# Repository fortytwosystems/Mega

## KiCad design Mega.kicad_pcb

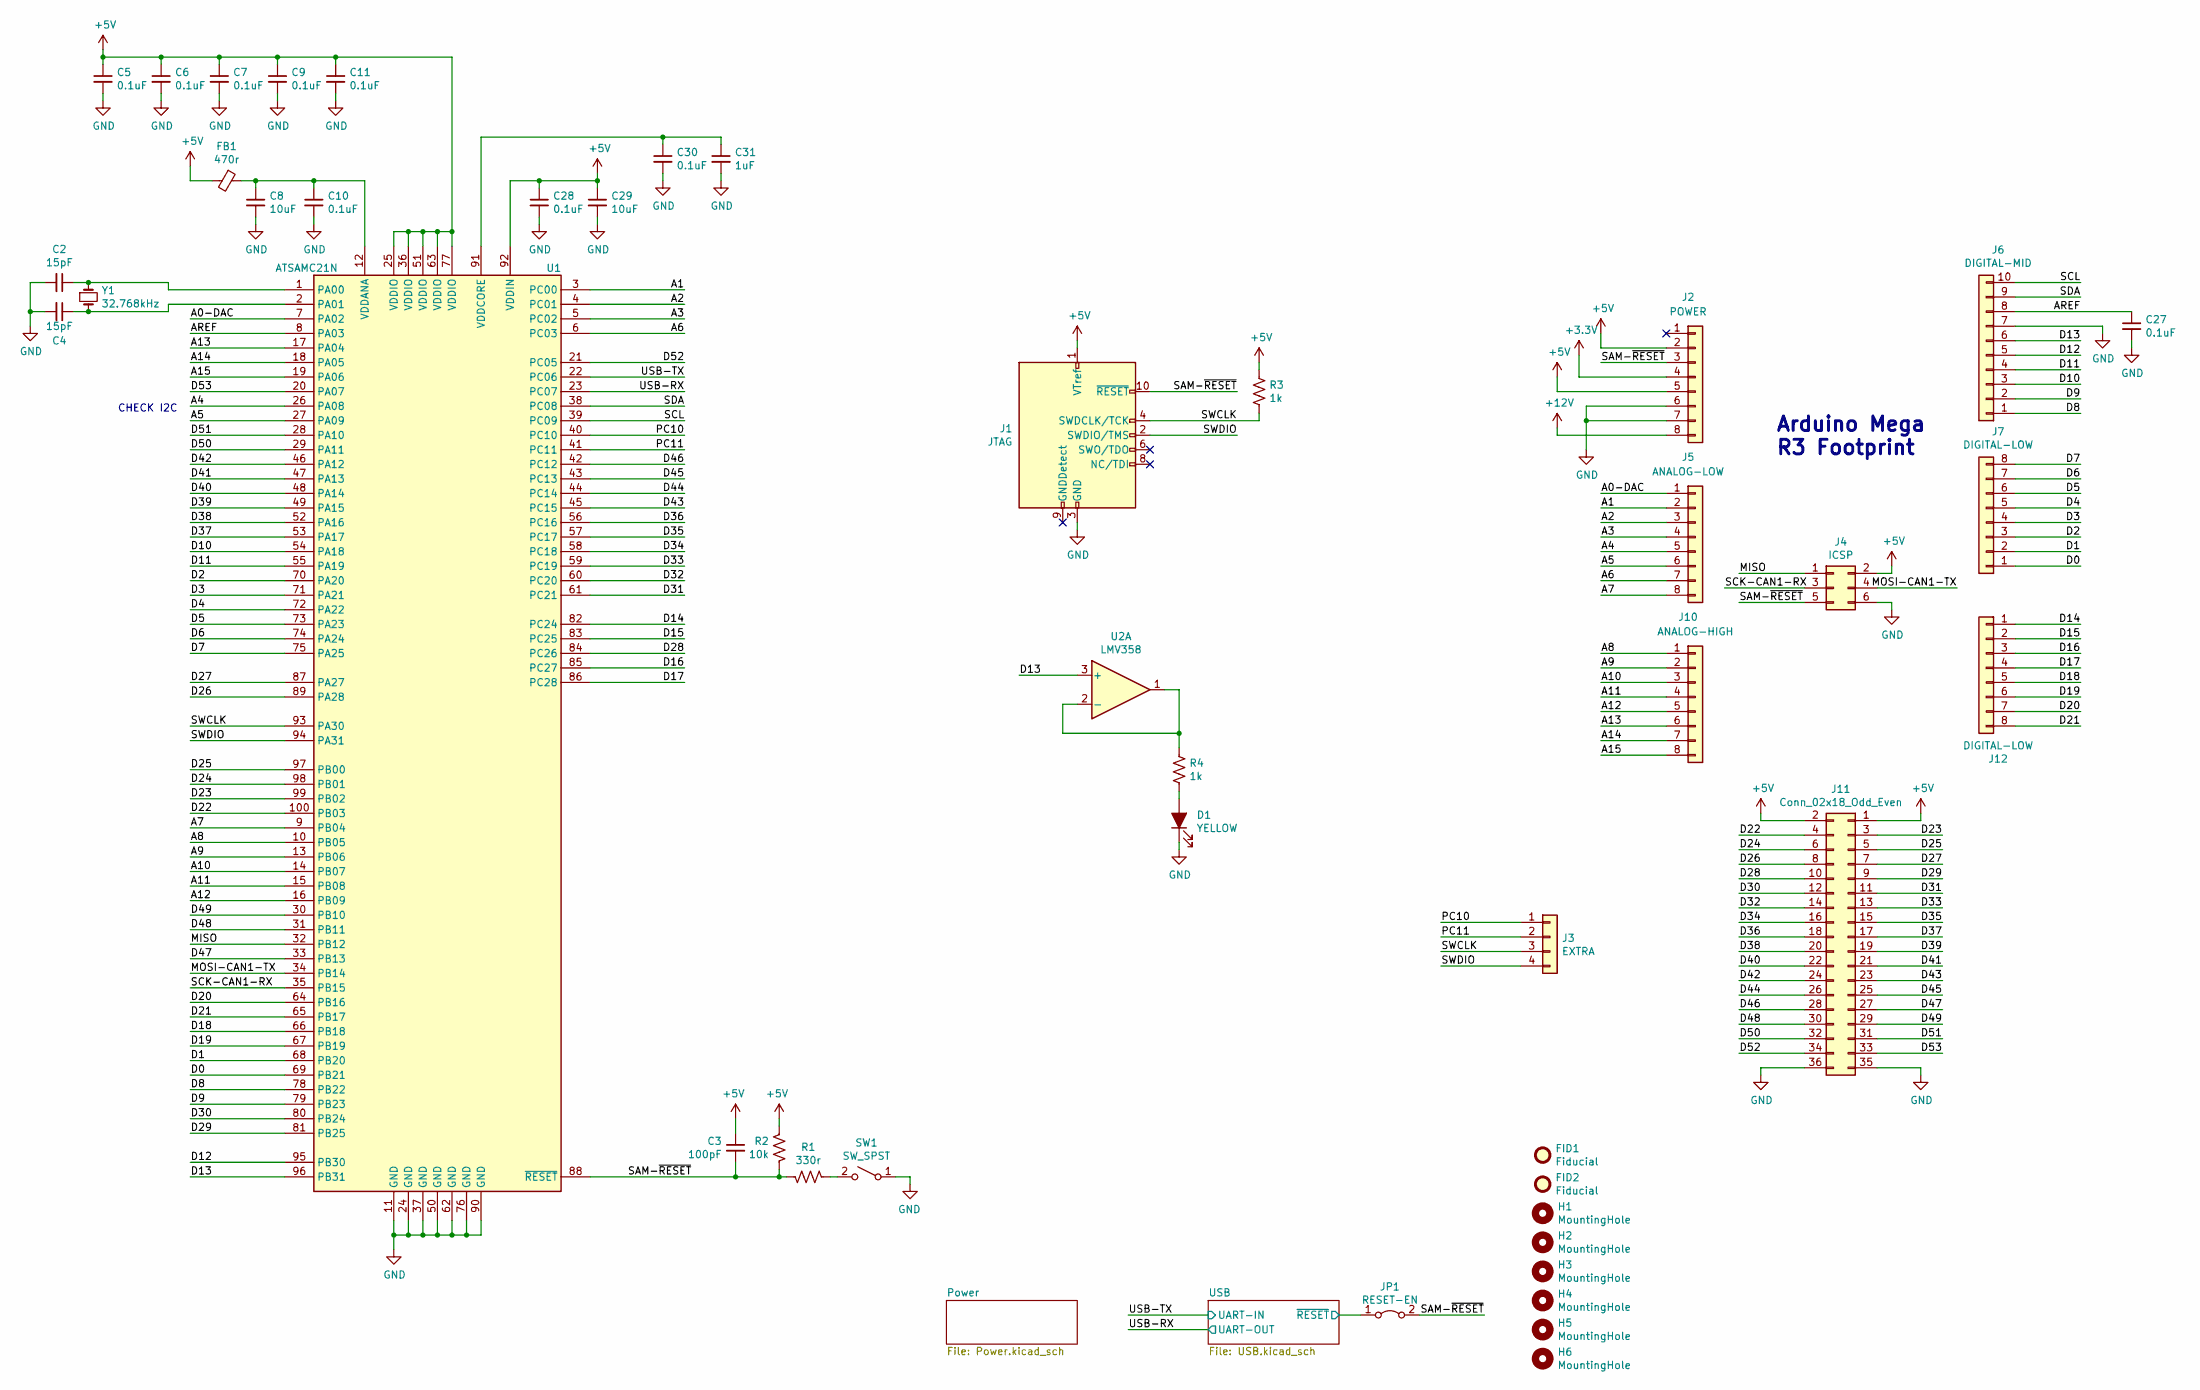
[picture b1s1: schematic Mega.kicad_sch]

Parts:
C2, C4: 15pF; C_0603_1608Metric
C3: 100pF; C_0603_1608Metric
C5, C6, C7, C9, C10, C11, C27, C28, C30: 0.1uF; C_0603_1608Metric
C8, C29: 10uF; C_0805_2012Metric
C31: 1uF; C_0805_2012Metric
D1: YELLOW; LED_0603_1608Metric
FB1: 470r; R_0603_1608Metric
FID1, FID2: Fiducial; Fiducial_0.75mm_Mask1.5mm
H1, H2, H3, H4, H5, H6: MountingHole; MountingHole_3.2mm_M3
J1: JTAG; PinHeader_2x05_P1.27mm_Vertical
J2: POWER; PinSocket_1x08_P2.54mm_Vertical
J3: EXTRA; PinHeader_1x04_P2.54mm_Vertical
J4: ICSP; PinHeader_2x03_P2.54mm_Vertical
J5: ANALOG-LOW; PinSocket_1x08_P2.54mm_Vertical
J6: DIGITAL-MID; PinSocket_1x10_P2.54mm_Vertical
J7, J12: DIGITAL-LOW; PinSocket_1x08_P2.54mm_Vertical
J10: ANALOG-HIGH; PinSocket_1x08_P2.54mm_Vertical
J11: Conn_02x18_Odd_Even; PinSocket_2x18_P2.54mm_Vertical
JP1: RESET-EN; SolderJumper-2_P1.3mm_Bridged_RoundedPad1.0x1.5mm
R1: 330r; R_0603_1608Metric
R2: 10k; R_0603_1608Metric
R3, R4: 1k; R_0603_1608Metric
SW1: SW_SPST; Button-CK-PTS525
U1: ATSAMC21N; TQFP-100_14x14mm_P0.5mm
U2: LMV358; VSSOP-8_3.0x3.0mm_P0.65mm
Y1: 32.768kHz; Crystal_SMD_MicroCrystal_CC7V-T1A-2Pin_3.2x1.5mm

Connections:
+12V: J2.8; also elsewhere on the board
/A0-DAC: J5.1, U1.7 (PA02)
/A1: J5.2, U1.3 (PC00)
/A2: J5.3, U1.4 (PC01)
/A3: J5.4, U1.5 (PC02)
/A4: J5.5, U1.26 (PA08)
/A5: J5.6, U1.27 (PA09)
/A6: J5.7, U1.6 (PC03)
/A7: J5.8, U1.9 (PB04)
/A8: J10.1, U1.10 (PB05)
/A9: J10.2, U1.13 (PB06)
/A10: J10.3, U1.14 (PB07)
/A11: J10.4, U1.15 (PB08)
/A12: J10.5, U1.16 (PB09)
/A13: J10.6, U1.17 (PA04)
/A14: J10.7, U1.18 (PA05)
/A15: J10.8, U1.19 (PA06)
/AREF: C27.1, J6.8, U1.8 (PA03)
/D0: J7.1, U1.69 (PB21)
/D1: J7.2, U1.68 (PB20)
/D2: J7.3, U1.70 (PA20)
/D3: J7.4, U1.71 (PA21)
/D4: J7.5, U1.72 (PA22)
/D5: J7.6, U1.73 (PA23)
/D6: J7.7, U1.74 (PA24)
/D7: J7.8, U1.75 (PA25)
/D8: J6.1, U1.78 (PB22)
/D9: J6.2, U1.79 (PB23)
/D10: J6.3, U1.54 (PA18)
/D11: J6.4, U1.55 (PA19)
/D12: J6.5, U1.95 (PB30)
/D14: J12.1, U1.82 (PC24)
/D15: J12.2, U1.83 (PC25)
/D16: J12.3, U1.85 (PC27)
/D17: J12.4, U1.86 (PC28)
/D18: J12.5, U1.66 (PB18)
/D19: J12.6, U1.67 (PB19)
/D20: J12.7, U1.64 (PB16)
/D21: J12.8, U1.65 (PB17)
/D22: J11.4, U1.100 (PB03)
/D23: J11.3, U1.99 (PB02)
/D24: J11.6, U1.98 (PB01)
/D25: J11.5, U1.97 (PB00)
/D26: J11.8, U1.89 (PA28)
/D27: J11.7, U1.87 (PA27)
/D28: J11.10, U1.84 (PC26)
/D29: J11.9, U1.81 (PB25)
/D30: J11.12, U1.80 (PB24)
/D31: J11.11, U1.61 (PC21)
/D32: J11.14, U1.60 (PC20)
/D33: J11.13, U1.59 (PC19)
/D34: J11.16, U1.58 (PC18)
/D35: J11.15, U1.57 (PC17)
/D36: J11.18, U1.56 (PC16)
/D37: J11.17, U1.53 (PA17)
/D38: J11.20, U1.52 (PA16)
/D39: J11.19, U1.49 (PA15)
/D40: J11.22, U1.48 (PA14)
/D41: J11.21, U1.47 (PA13)
/D42: J11.24, U1.46 (PA12)
/D43: J11.23, U1.45 (PC15)
/D44: J11.26, U1.44 (PC14)
/D45: J11.25, U1.43 (PC13)
/D46: J11.28, U1.42 (PC12)
/D47: J11.27, U1.33 (PB13)
/D48: J11.30, U1.31 (PB11)
/D49: J11.29, U1.30 (PB10)
/D50: J11.32, U1.29 (PA11)
/D51: J11.31, U1.28 (PA10)
/D52: J11.34, U1.21 (PC05)
/D53: J11.33, U1.20 (PA07)
/MISO: J4.1, U1.32 (PB12)
/MOSI-CAN1-TX: J4.4, U1.34 (PB14)
/PC10: J3.1, U1.40 (PC10)
/PC11: J3.2, U1.41 (PC11)
/SAM-~RESET~: C3.2, J1.10 (~RESET~), J2.3, J4.5, JP1.2 (B), R1.1, R2.1, U1.88 (~RESET)
/SCK-CAN1-RX: J4.3, U1.35 (PB15)
/SCL: J6.10, U1.39 (PC09)
/SDA: J6.9, U1.38 (PC08)
/SWCLK: J1.4 (SWDCLK/TCK), J3.3, R3.2, U1.93 (PA30)
/SWDIO: J1.2 (SWDIO/TMS), J3.4, U1.94 (PA31)
/USB-RX: U1.23 (PC07); also elsewhere on the board
/USB-TX: U1.22 (PC06); also elsewhere on the board
/USB/~RESET: JP1.1 (A); also elsewhere on the board
GND: C2.2, C4.2, C5.2, C6.2, C7.2, C8.2, C9.2, C10.2, C11.2, C27.2, C28.2, C29.2, C30.2, C31.2, D1.1 (K), J1.3 (GND), J1.5 (GND), J2.6, J2.7, J4.6, J6.7, J11.35, J11.36, SW1.1 (A), U1.11 (GND), U1.24 (GND), U1.37 (GND), U1.50 (GND), U1.62 (GND), U1.76 (GND), U1.90 (GND); also elsewhere on the board
unnamed: C2.1, U1.1 (PA00), Y1.1
unnamed: C4.1, U1.2 (PA01), Y1.2
unnamed: C8.1, C10.1, FB1.1, U1.12 (VDDANA)
unnamed: C30.1, C31.1, U1.91 (VDDCORE)
unnamed: D1.2 (A), R4.2
unnamed: R1.2, SW1.2 (B)

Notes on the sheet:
CHECK I2C
Arduino Mega R3 Footprint

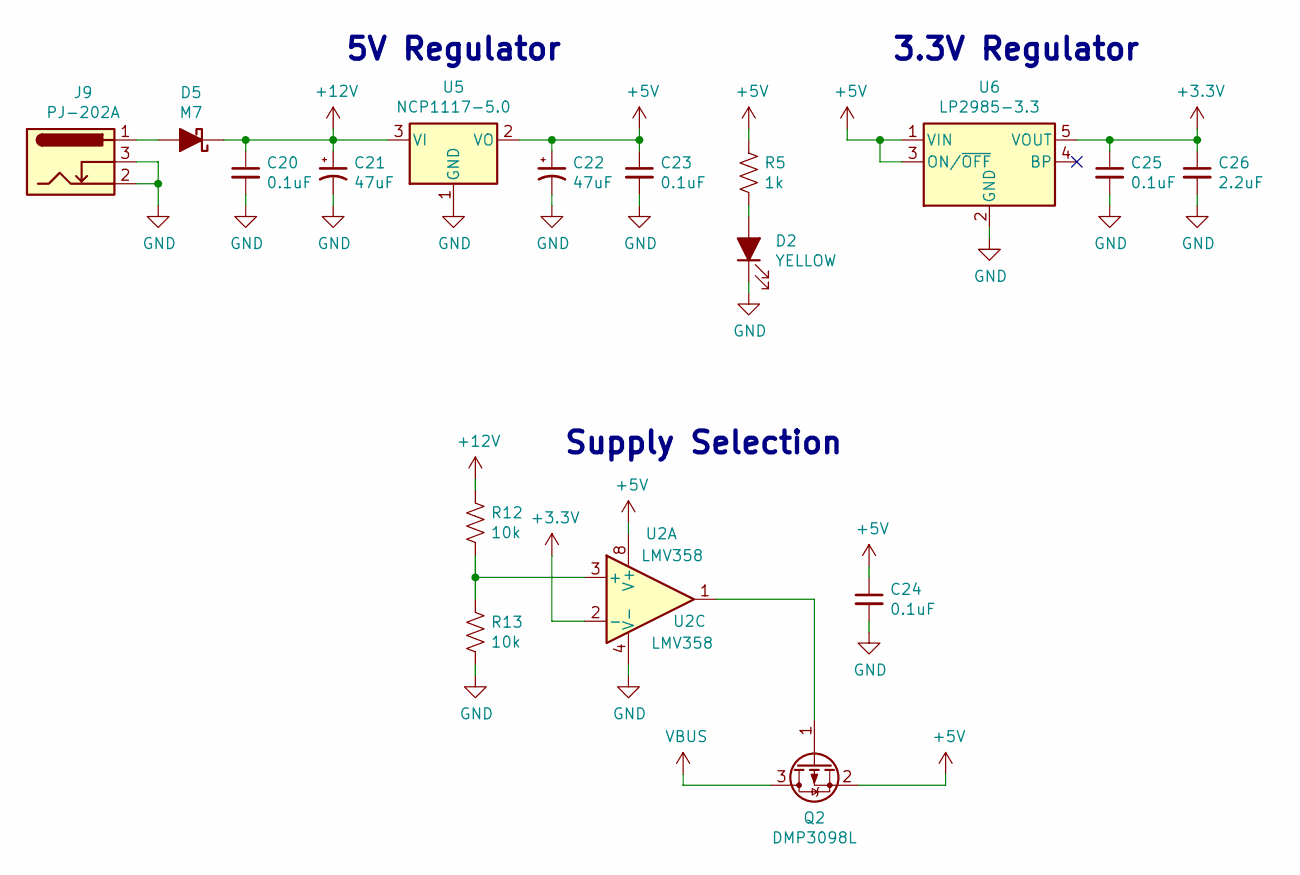
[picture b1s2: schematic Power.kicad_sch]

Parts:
C20, C23, C24, C25: 0.1uF; C_0603_1608Metric
C21, C22: 47uF; CP_Elec_6.3x5.4
C26: 2.2uF; C_0805_2012Metric
D2: YELLOW; LED_0603_1608Metric
D5: M7; D_SMA
J9: PJ-202A; Barrel-Jack-PJ-202A
Q2: DMP3098L; SOT-23
R5: 1k; R_0603_1608Metric
R12, R13: 10k; R_0603_1608Metric
U2: LMV358; VSSOP-8_3.0x3.0mm_P0.65mm
U5: NCP1117-5.0; SOT-223-3_TabPin2
U6: LP2985-3.3; SOT-23-5

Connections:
+12V: C20.1, C21.1, D5.1 (K), R12.1, U5.3 (VI); also elsewhere on the board
GND: C20.2, C21.2, C22.2, C23.2, C24.2, C25.2, C26.2, D2.1 (K), J9.2, J9.3, R13.2, U2.4 (V-), U5.1 (GND), U6.2 (GND); also elsewhere on the board
unnamed: D2.2 (A), R5.2
unnamed: D5.2 (A), J9.1
VBUS: Q2.3 (D); also elsewhere on the board

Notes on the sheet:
5V Regulator
Supply Selection
3.3V Regulator

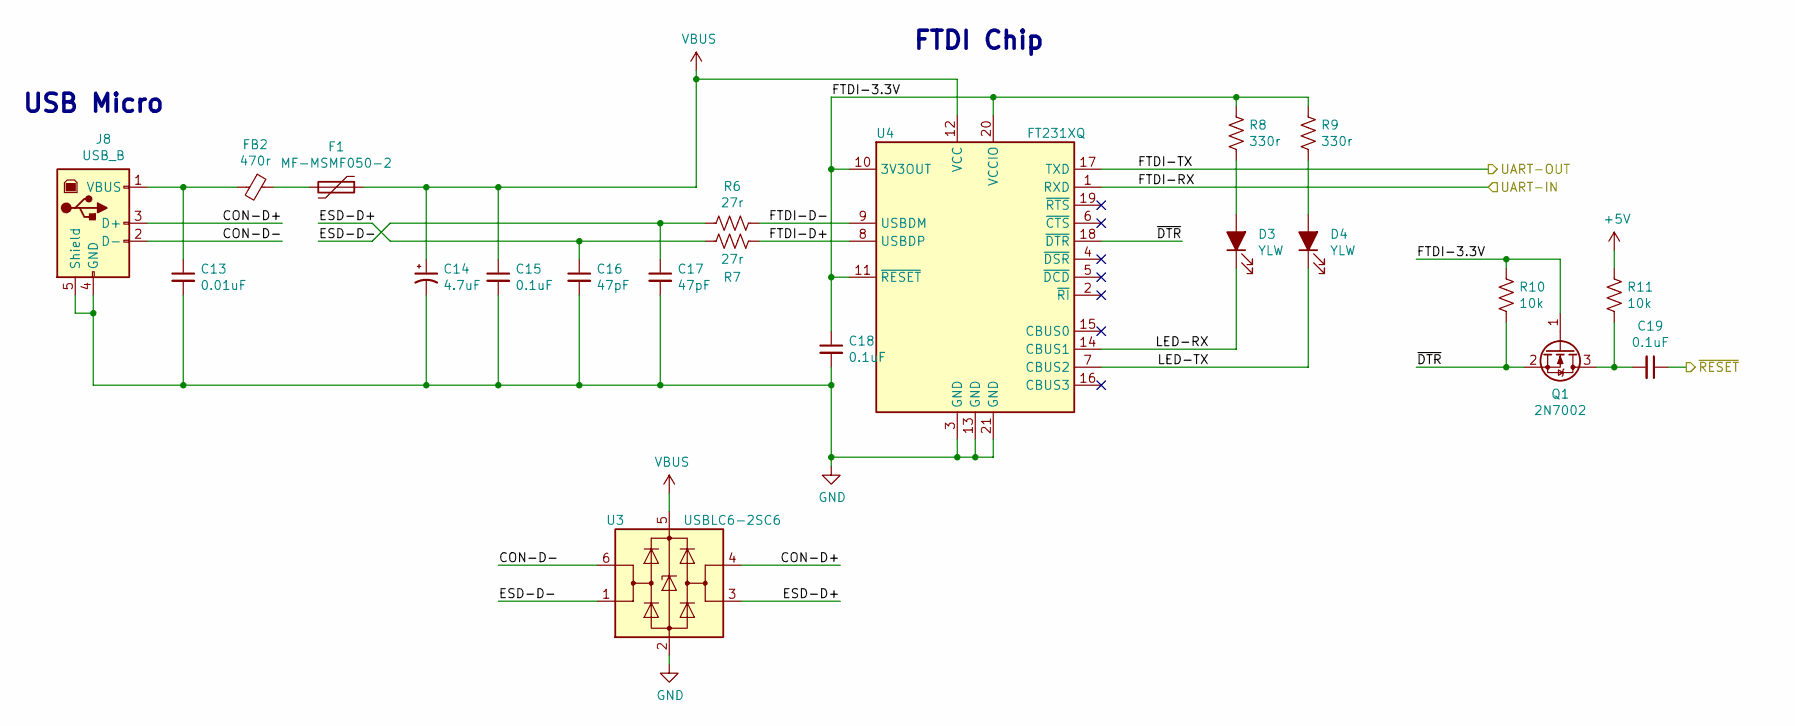
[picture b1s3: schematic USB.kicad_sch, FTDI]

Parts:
C13: 0.01uF; C_0603_1608Metric
C14: 4.7uF; CP_EIA-3216-18_Kemet-A
C15, C18, C19: 0.1uF; C_0603_1608Metric
C16, C17: 47pF; C_0603_1608Metric
D3, D4: YLW; LED_0603_1608Metric
F1: MF-MSMF050-2; Fuse_1812_4532Metric
FB2: 470r; R_0603_1608Metric; Part Number BLM18PG471SN1; Digikey PN 490-5223-1-ND
J8: USB_B; USB-B-Amphenol-61729-1011BLF
Q1: 2N7002; SOT-23
R6, R7: 27r; R_0603_1608Metric
R8, R9: 330r; R_0603_1608Metric
R10, R11: 10k; R_0603_1608Metric
U3: USBLC6-2SC6; SOT-23-6
U4: FT231XQ; QFN-20-1EP_4x4mm_P0.5mm_EP2.5x2.5mm

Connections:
/USB-RX: U4.17 (TXD); also elsewhere on the board
/USB-TX: U4.1 (RXD); also elsewhere on the board
/USB/CON-D+: J8.3 (D+), U3.4 (I/O2)
/USB/CON-D-: J8.2 (D-), U3.6 (I/O1)
/USB/ESD-D+: C16.1, R7.2, U3.3 (I/O2)
/USB/ESD-D-: C17.1, R6.2, U3.1 (I/O1)
/USB/FTDI-3.3V: C18.1, Q1.1 (G), R8.1, R9.1, R10.1, U4.10 (3V3OUT), U4.11 (~RESET), U4.20 (VCCIO)
/USB/FTDI-D+: R7.1, U4.8 (USBDP)
/USB/FTDI-D-: R6.1, U4.9 (USBDM)
/USB/LED-RX: D3.1 (K), U4.14 (CBUS1)
/USB/LED-TX: D4.1 (K), U4.7 (CBUS2)
/USB/~DTR~: Q1.2 (S), R10.2, U4.18 (~DTR)
/USB/~RESET: C19.1; also elsewhere on the board
GND: C13.2, C14.2, C15.2, C16.2, C17.2, C18.2, J8.4 (GND), J8.5 (Shield), U3.2 (GND), U4.3 (GND), U4.13 (GND), U4.21 (GND); also elsewhere on the board
unnamed: C13.1, FB2.2, J8.1 (VBUS)
unnamed: C19.2, Q1.3 (D), R11.2
unnamed: D3.2 (A), R8.2
unnamed: D4.2 (A), R9.2
unnamed: F1.2, FB2.1
VBUS: C14.1, C15.1, F1.1, U3.5 (VBUS), U4.12 (VCC); also elsewhere on the board

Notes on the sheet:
USB Micro
FTDI Chip

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
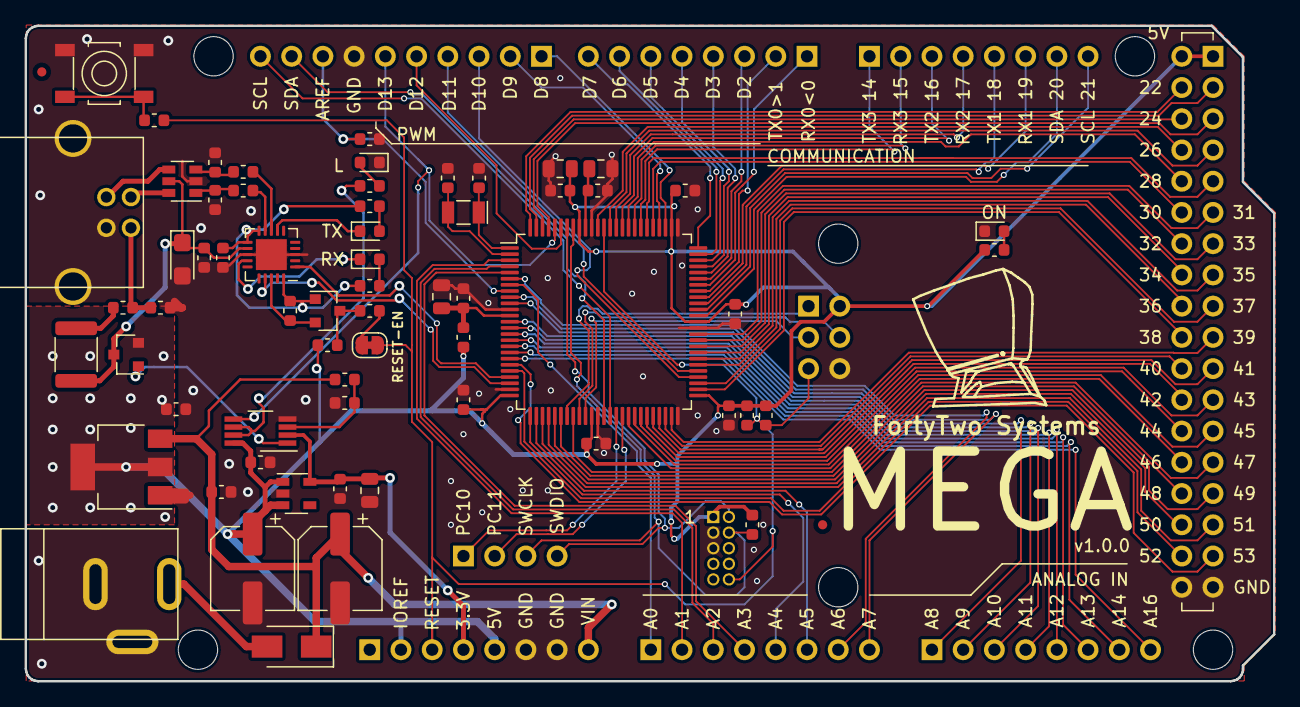
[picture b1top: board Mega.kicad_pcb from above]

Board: 2 copper layers, 101.5 x 53.3 mm, 81 parts (0 on the bottom side), 115 nets.

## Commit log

2021-03-28 Initial GitHub commit
2021-03-28 Create LICENSE
2021-05-04 Fix crossed SWD traces and move to KiCAD 5.99
2021-05-04 Add PDF schematics
